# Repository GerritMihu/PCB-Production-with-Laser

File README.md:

# PCB Production with a Laser

🇩🇪 [Deutsche Version](README.de.md)

Documentation of PCB fabrication in our school workshop: copper is **removed directly by the laser** (ablation) – no photoresist, no etching, no chemicals.

The documentation is machine-independent: the process lives in `docs/`, machine-specific data and parameters in `machines/<machine>/`.

## Machines

| | [xTool F2 Ultra](machines/xtool-f2-ultra/README.md) | [Trotec Speedy](machines/trotec-speedy/README.md) |
|---|---|---|
| Status | in use | trial planned |
| Process | copper ablation (fiber) | TODO |
| Min. track width | 0.4 mm | TODO |
| Copper–copper clearance | 0.2 mm | TODO |
| Copper–edge clearance | 1.0 mm | TODO |
| Via (drill / pad) | 0.8 / 1.6 mm | TODO |
| Solder mask | no working process yet | TODO |
| Software | xTool Studio | TODO |
| Linux | Wine: installs & launches, device test pending – [Linux test](machines/xtool-f2-ultra/software-linux.md) | TODO |

## Contents

1. [Overview & workflow](docs/en/01-overview.md)
2. [Safety](docs/en/02-safety.md)
3. [Design rules (KiCad)](docs/en/03-design-rules.md)
4. [Export: KiCad → laser](docs/en/04-export.md)
5. [Post-processing](docs/en/05-post-processing.md)
6. [Common defects](docs/en/06-defects.md)
7. [Student quick guide](docs/en/07-student-guide.md)
8. [**Manual path step by step:** KiCad → xTool](docs/en/08-guide-manual.md)
9. [**Automatic path:** KiBot + GitHub Actions](docs/en/09-guide-automatic.md)

## Repository layout

```
docs/de, docs/en       process (machine-independent)
machines/<machine>/    machine data, laser parameters, presets, software
kicad/template/        KiCad project template with matching design rules
kibot/                 KiBot config for laser export (DXF + SVG + Gerber)
examples/              example projects incl. auto-generated laser files
images/                photos and graphics
```

## Adding a machine

1. Copy `machines/trotec-speedy/` → `machines/<new-machine>/`
2. Add a column to the table above (DE + EN)
3. If different design rules are needed: add a template under `kicad/template/Laser_PCB_<machine>/`

## License

[CC BY-SA 4.0](LICENSE)

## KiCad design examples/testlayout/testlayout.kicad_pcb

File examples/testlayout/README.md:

# Test layout for fabrication methods

🇩🇪 [Deutsch](README.de.md) · [← Overview](../../README.md)

Standardised test board (100 × 80 mm, single-sided F.Cu) for comparing fabrication methods under identical conditions:

1. Direct laser ablation (xTool F2 Ultra, fiber laser)
2. Laser mask + etching (laser removes paint, then ferric chloride)
3. CNC isolation milling
4. Classic etching (toner transfer or similar)

## Test structures

| Field | Content | Check |
|---|---|---|
| Track width | Tracks 0.10 / 0.15 / 0.20 / 0.30 / 0.40 / 0.50 mm, 30 mm long between two test pads | Continuity and resistance (multimeter), width under magnifier/microscope |
| Clearance | Comb structures with gaps 0.10 … 0.50 mm (track width 0.4 mm) | Isolation between pad A and pad B (multimeter: no continuity) |
| SMD | 0603, 0805, 1206, SOT-23, SOIC-8, TSSOP-14 (KiCad standard library) | Pads complete and separated? Test assembly |
| THT | Drill/pad 0.6/1.2 · 0.8/1.6 · 1.0/2.0 · 1.2/2.4 mm | Annular ring after drilling, alignment |
| Text | Copper text 1.0 / 1.5 / 2.0 mm | Legibility |
| Scale | 50 mm (X) and 20 mm (Y) with ticks | Dimensional accuracy with calipers |

The template's design rules are deliberately lowered for this project (min. 0.1 mm) so the test structures pass DRC. Normal projects keep the values from [design rules](../../docs/en/03-design-rules.md).

## Procedure and measurement sheet

See the German version [README.de.md](README.de.md) for the full procedure and the measurement sheet.

## Files

- `generate_testlayout.py` creates `testlayout.kicad_pcb` and `testlayout.kicad_pro` (values editable at the top of the script). Open in KiCad and run DRC afterwards.
- The KiBot workflow generates the laser files (DXF, SVG, Gerber) automatically in `laser/`.

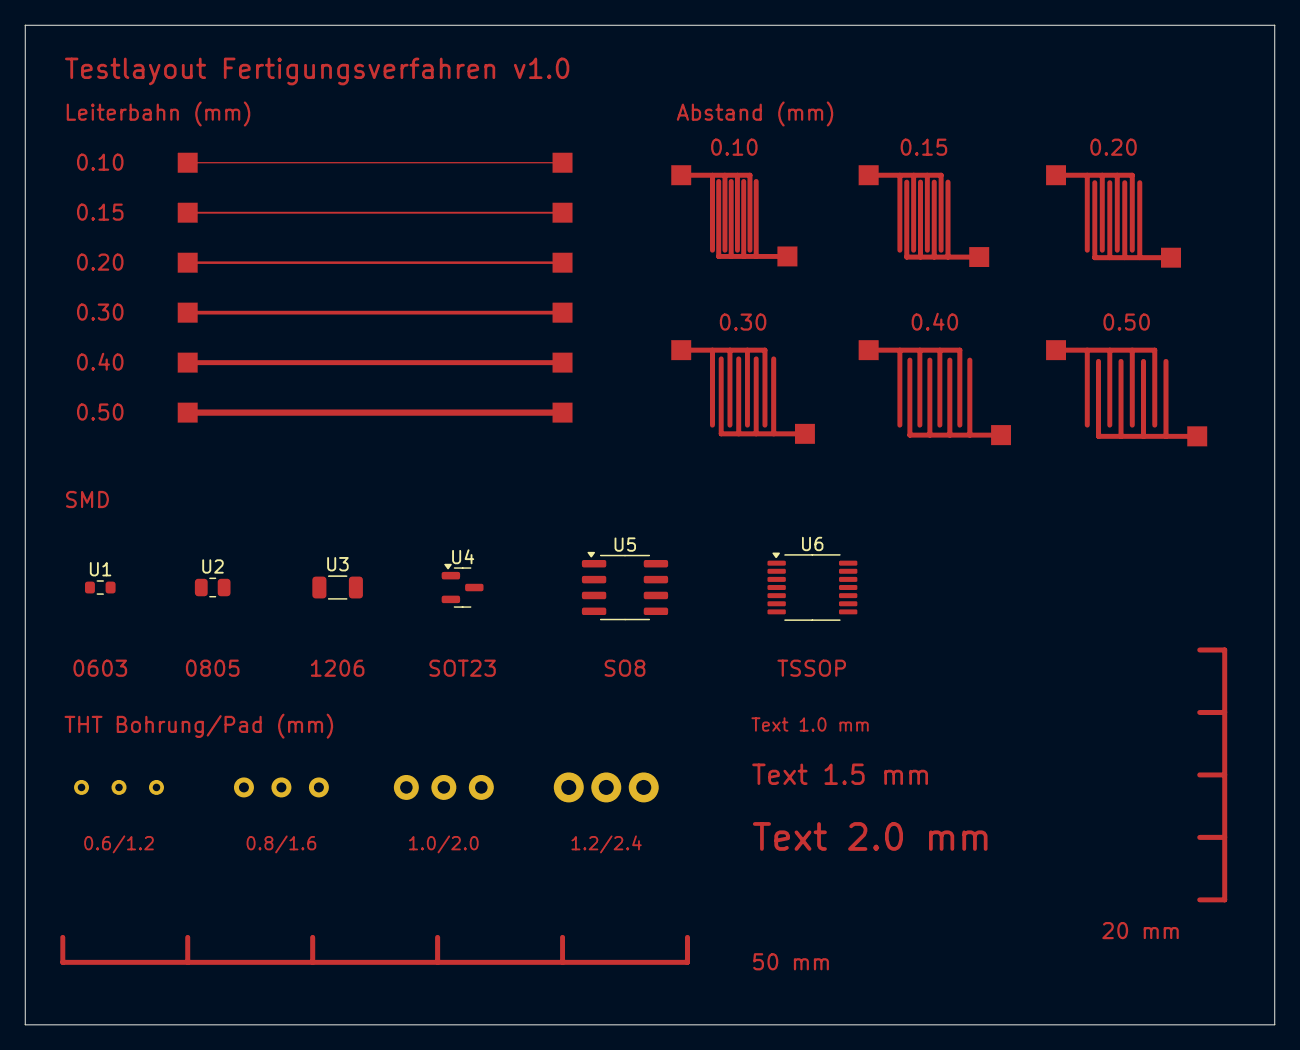
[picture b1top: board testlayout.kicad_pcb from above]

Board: 2 copper layers, 100.0 x 80.0 mm, 34 parts (0 on the bottom side), 6 nets.

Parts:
H1: Bohrung 0.6 / Pad 1.2; THT_D0.6_P1.2
H2: Bohrung 0.8 / Pad 1.6; THT_D0.8_P1.6
H3: Bohrung 1 / Pad 2; THT_D1_P2
H4: Bohrung 1.2 / Pad 2.4; THT_D1.2_P2.4
TP1, TP2, TP3, TP4, TP5, TP6, TP7, TP8, TP9, TP10, TP11, TP12, TP13, TP14, TP15, TP16, TP17, TP18, TP19, TP20, TP21, TP22, TP23, TP24: Testpad; Testpad_1.6mm
U1: R_0603_1608Metric
U2: R_0805_2012Metric
U3: R_1206_3216Metric
U4: SOT-23
U5: SOIC-8_3.9x4.9mm_P1.27mm
U6: TSSOP-14_4.4x5mm_P0.65mm

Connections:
BAHN_010: TP1.1, TP2.1
BAHN_015: TP3.1, TP4.1
BAHN_020: TP5.1, TP6.1
BAHN_030: TP7.1, TP8.1
BAHN_040: TP9.1, TP10.1
BAHN_050: TP11.1, TP12.1
